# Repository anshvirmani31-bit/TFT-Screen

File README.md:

# TFT-Screen
This is my project for half life week 4. I'm designing a TFT screen that can display simple numbers and be controlled with a rotary encoder. It uses a raspberry pi pico as the micro controller.

# What is it?

This is a simple TFT screen that uses a CANADUINO® ST7789 TFT IPS 1.3-inch display. The interface is controlled using a rotary encoder and it uses raspberry pi pico as the brain. The pcb is designed using KiCad.

# How is it unique

My TFT screen is unique as it's much simpler than what's shown in the tutorial. It doesn't use nearly as many parts and the firmware is also much simpler. My screen also has less pins and I use a raspberry pi pico instead of a XIAO so I had to adapt that in the firmware and schematic accordingly.

# Images

## KiCad Schematic

## KiCad pcb

### Normal view

### 3D view

# BOM

|Item                    |Qty|Supplier  |Cost/item|Total Cost|link                                                                                       |
|------------------------|---|----------|---------|----------|-------------------------------------------------------------------------------------------|
|CANADUINO® ST7789       |1  |Amazon    |$4.29    |$4.29     |https://www.amazon.ca/gp/product/B088CQ4GPT/ref=ox_sc_act_title_1?smid=A29AOP4GIE7DX6&psc=1|
|PCB                     |1  |JLCPCB    |$4.00    |$4.00     |https://jlcpcb.com                                                                         |
|Raspberry Pi Pico       |1  |AliExpress|$2.58    |$2.58     |https://www.aliexpress.com/item/1005005617180169.html                                      |
|Rotary Encoder          |1  |AliExpress|$1.01    |$1.01     |https://www.aliexpress.com/item/1005007644083514.html                                      |
|Low profile switch      |1  |Amazon    |$6.05    |$6.05     |https://www.amazon.ca/gp/product/B0C6FH6XQ7/ref=ox_sc_act_title_1?smid=A1XJHOP1YXWD49&psc=1|
|Estimated total shipping|1  |          |         |$8.77     |                                                                                           |

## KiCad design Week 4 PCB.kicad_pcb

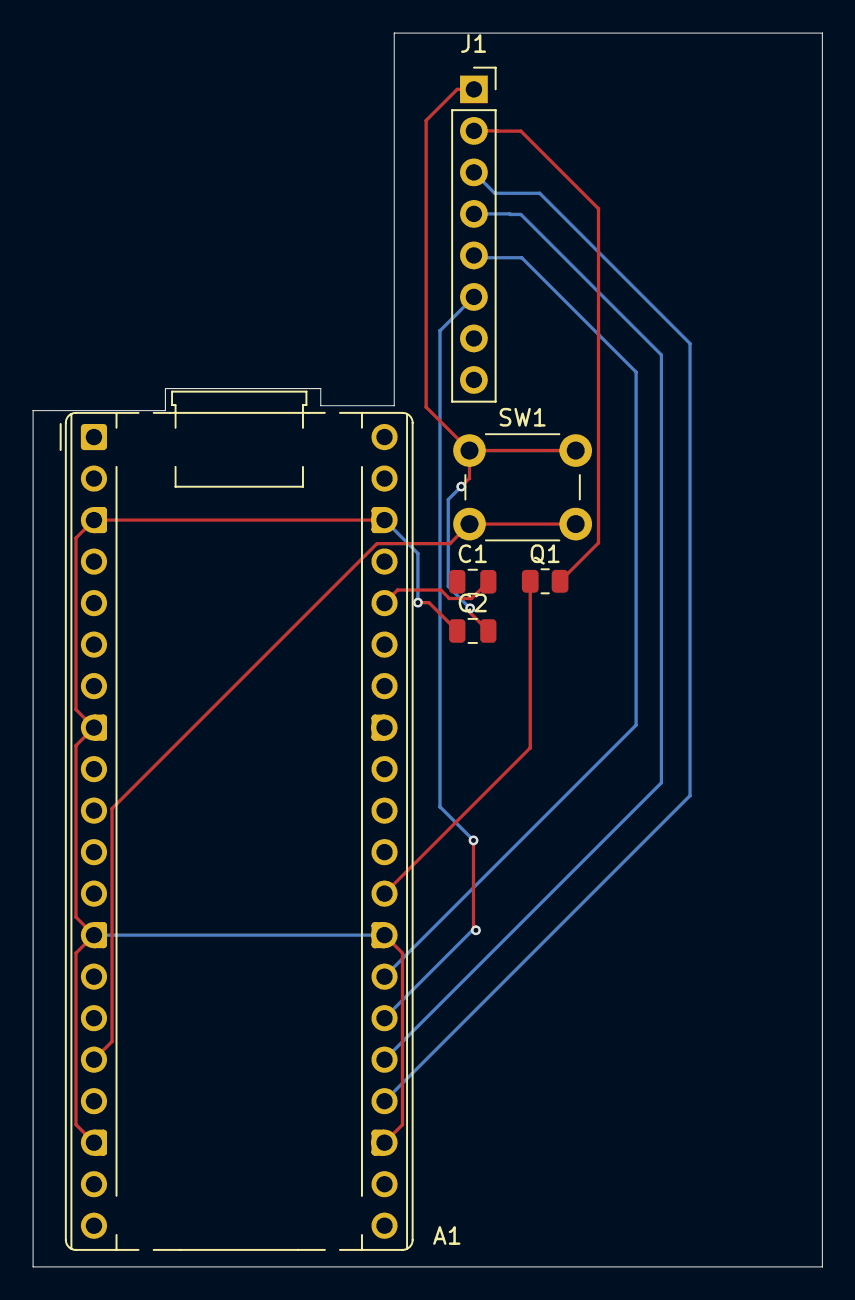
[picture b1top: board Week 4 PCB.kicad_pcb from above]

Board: 2 copper layers, 48.3 x 75.5 mm, 6 parts (0 on the bottom side), 10 nets.

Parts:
A1: RaspberryPi_Pico; RaspberryPi_Pico_Common_THT
C1, C2: C_Small; C_0805_2012Metric
J1: Conn_01x07; PinSocket_1x08_P2.54mm_Vertical
Q1: AO3401A; R_0805_2012Metric
SW1: SW_Push; SW_PUSH_6mm

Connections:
+3V3: J1.2, Q1.2 (S)
/BLK: A1.29 (GPIO22), Q1.1 (G)
/DC: A1.26 (GPIO20), J1.6
/RES: A1.27 (GPIO21), J1.5
/SCK: A1.24 (GPIO18), J1.3
/SDA: A1.25 (GPIO19), J1.4
GND: C2.2, J1.1, SW1.1
unnamed: A1.36 (3V3), C1.2
unnamed: A1.3 (GND), A1.8 (GND), A1.13 (GND), A1.18 (GND), A1.23 (GND), A1.28 (GND), A1.38 (GND), C2.1
unnamed: A1.16 (GPIO12), SW1.2
